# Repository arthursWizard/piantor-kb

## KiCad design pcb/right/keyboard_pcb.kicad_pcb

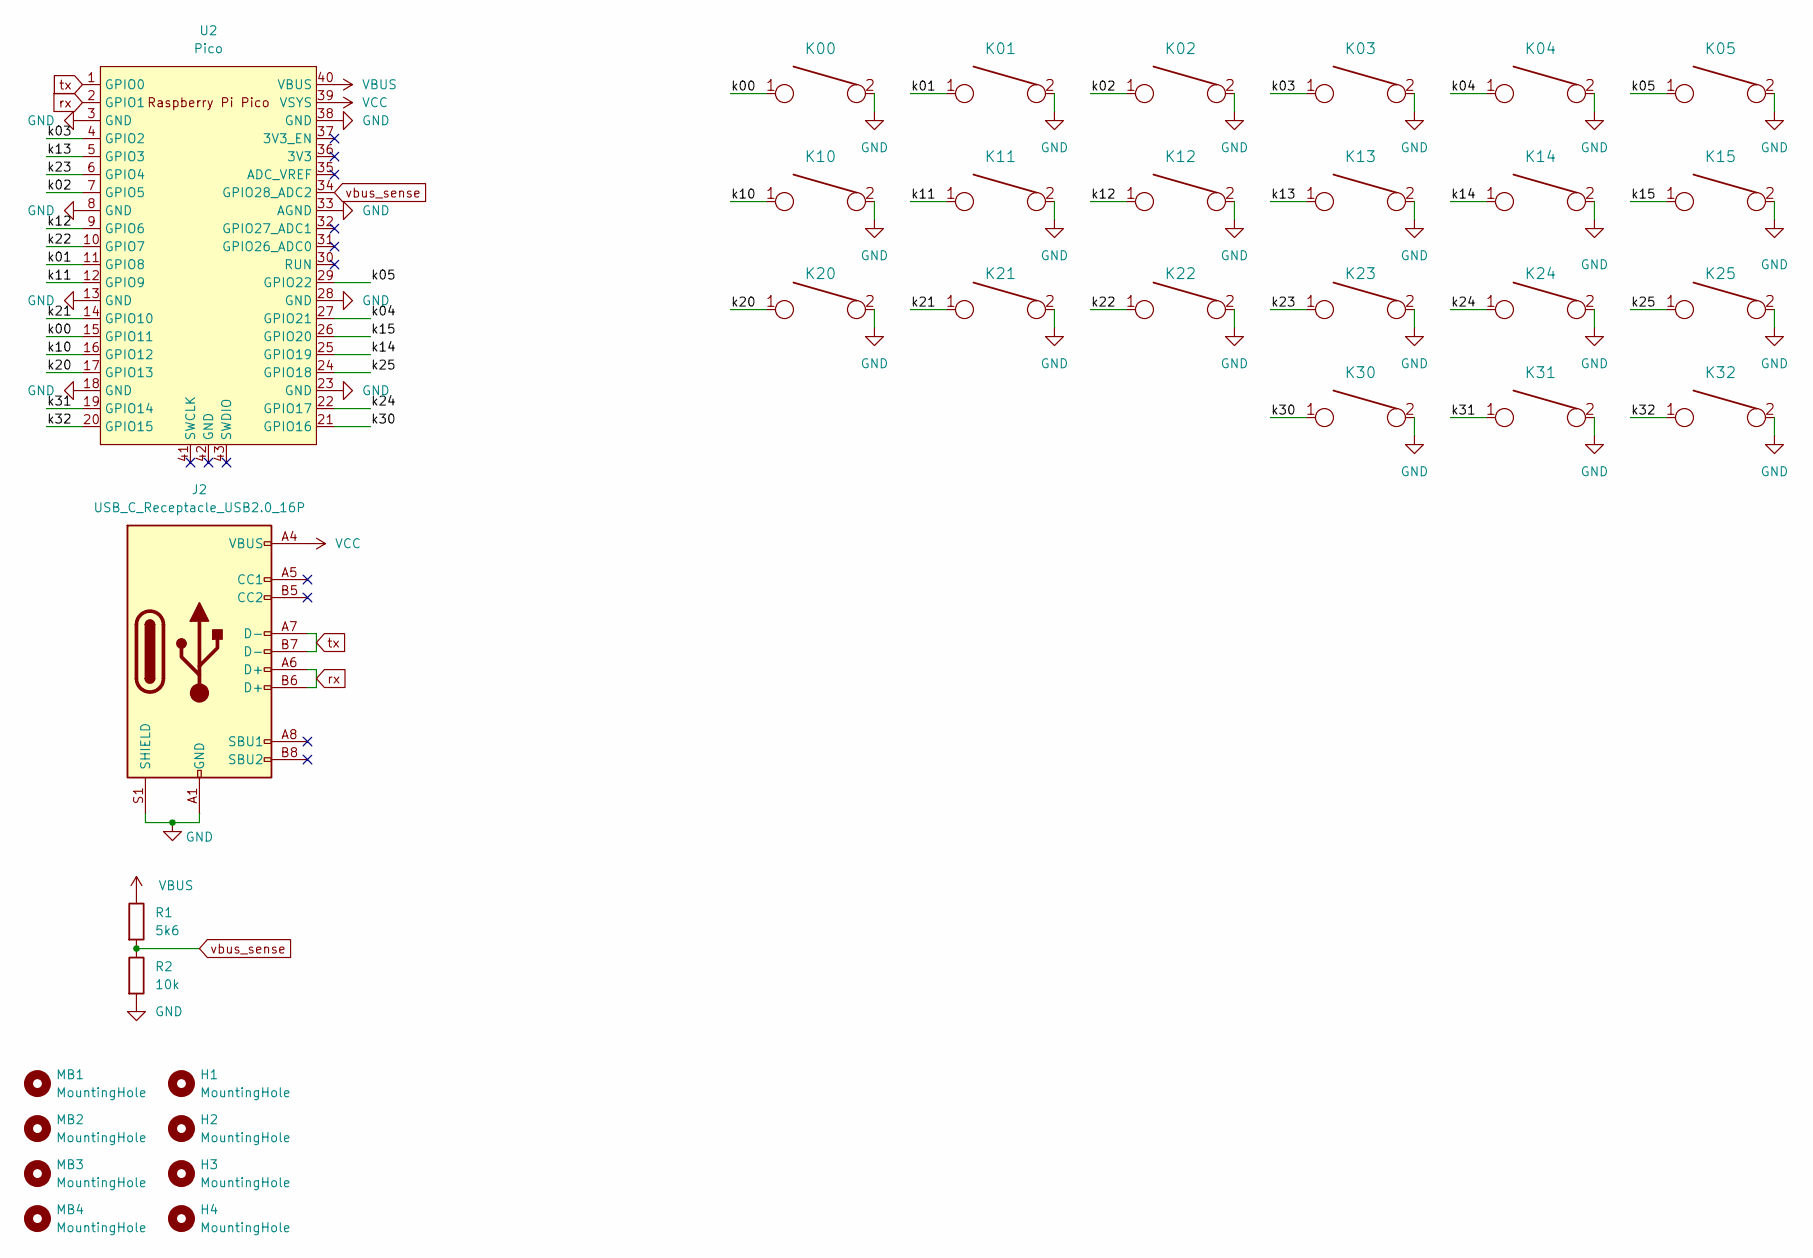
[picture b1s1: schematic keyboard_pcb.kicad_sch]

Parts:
H1, H2, H3, H4: MountingHole; MountingHole_2.2mm_M2-8mm
J2: USB_C_Receptacle_USB2.0_16P; USB_C_Receptacle_Palconn_UTC16-G
K00, K01, K02, K03, K04, K05, K10, K11, K12, K13, K14, K15, K20, K21, K22, K23, K24, K25, K30, K31, K32: KEYSW; SW_PG1350_reversible
MB1, MB2, MB3, MB4: MountingHole; mousebites
R1: 5k6; R_1206_3216Metric_Pad1.30x1.75mm_HandSolder
R2: 10k; R_1206_3216Metric_Pad1.30x1.75mm_HandSolder
U2: Pico; RPi_Pico_SMD_TH

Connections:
/k00: K00.1, U2.15 (GPIO11)
/k01: K01.1, U2.11 (GPIO8)
/k02: K02.1, U2.7 (GPIO5)
/k03: K03.1, U2.4 (GPIO2)
/k04: K04.1, U2.27 (GPIO21)
/k05: K05.1, U2.29 (GPIO22)
/k10: K10.1, U2.16 (GPIO12)
/k11: K11.1, U2.12 (GPIO9)
/k12: K12.1, U2.9 (GPIO6)
/k13: K13.1, U2.5 (GPIO3)
/k14: K14.1, U2.25 (GPIO19)
/k15: K15.1, U2.26 (GPIO20)
/k20: K20.1, U2.17 (GPIO13)
/k21: K21.1, U2.14 (GPIO10)
/k22: K22.1, U2.10 (GPIO7)
/k23: K23.1, U2.6 (GPIO4)
/k24: K24.1, U2.22 (GPIO17)
/k25: K25.1, U2.24 (GPIO18)
/k30: K30.1, U2.21 (GPIO16)
/k31: K31.1, U2.19 (GPIO14)
/k32: K32.1, U2.20 (GPIO15)
GND: J2.A1 (GND), J2.A12 (GND), J2.B1 (GND), J2.B12 (GND), J2.S1 (SHIELD), K00.2, K01.2, K02.2, K03.2, K04.2, K05.2, K10.2, K11.2, K12.2, K13.2, K14.2, K15.2, K20.2, K21.2, K22.2, K23.2, K24.2, K25.2, K30.2, K31.2, K32.2, R2.2, U2.3 (GND), U2.8 (GND), U2.13 (GND), U2.18 (GND), U2.23 (GND), U2.28 (GND), U2.33 (AGND), U2.38 (GND)
VBUS: R1.1, U2.40 (VBUS)
VCC: J2.A4 (VBUS), J2.A9 (VBUS), J2.B4 (VBUS), J2.B9 (VBUS), U2.39 (VSYS)
rx: J2.A6 (D+), J2.B6 (D+), U2.2 (GPIO1)
tx: J2.A7 (D-), J2.B7 (D-), U2.1 (GPIO0)
vbus_sense: R1.2, R2.1, U2.34 (GPIO28_ADC2)

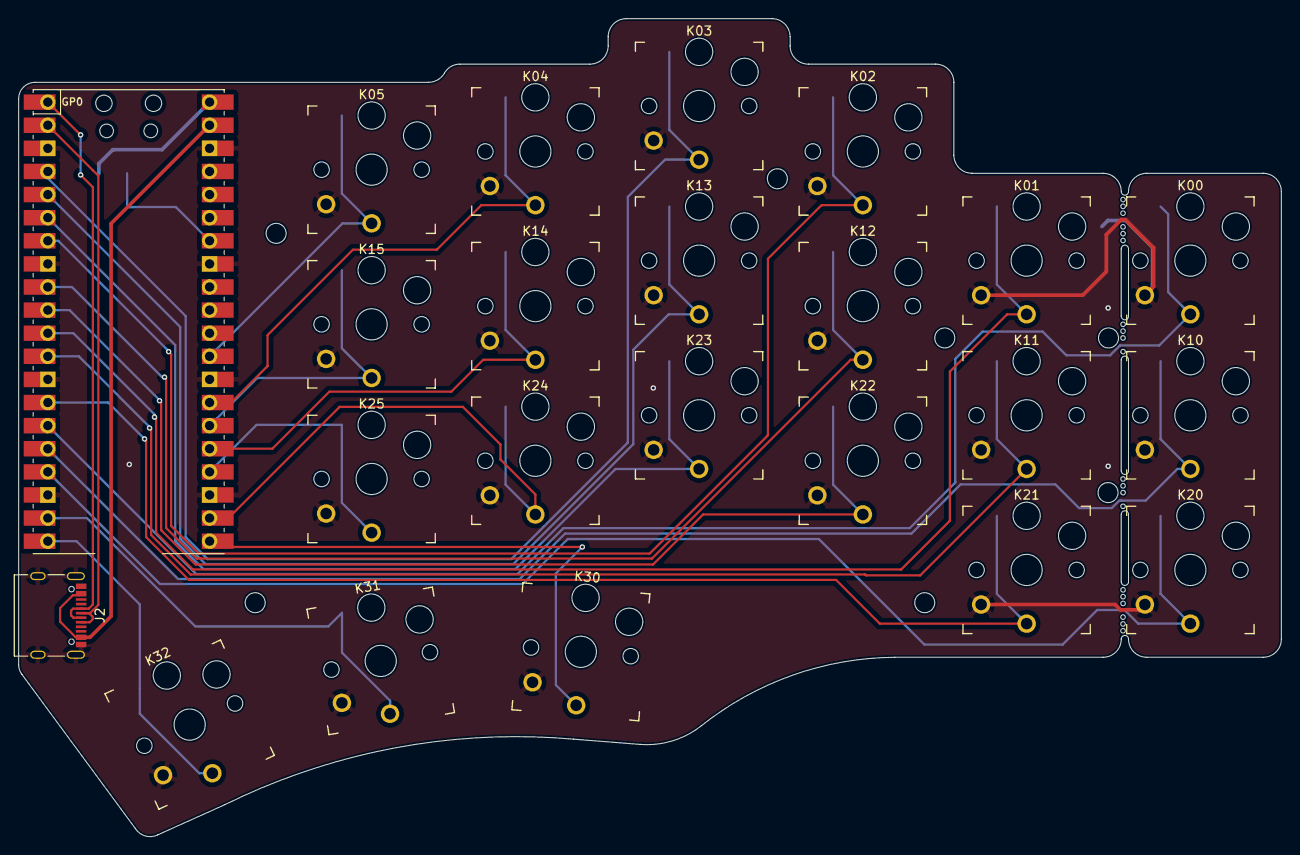
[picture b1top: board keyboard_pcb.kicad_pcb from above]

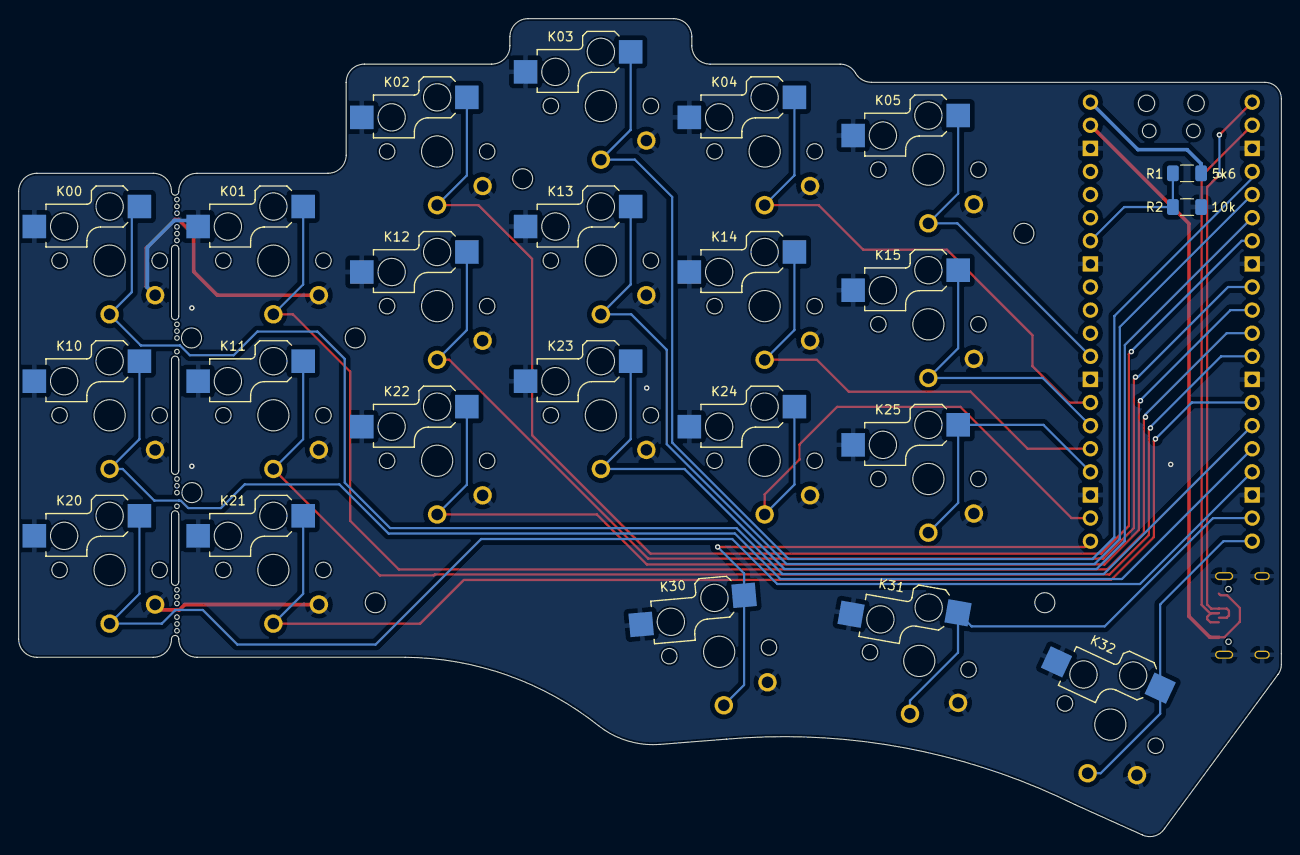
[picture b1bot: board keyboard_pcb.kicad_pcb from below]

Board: 2 copper layers, 138.8 x 89.9 mm, 36 parts (13 on the bottom side), 27 nets.

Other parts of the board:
H1#2, H4#2, H4#3: MountingHole; MountingHole_2.2mm_M2-8mm

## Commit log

2025-05-21 Replace TRRS with USB-C on left side
2025-05-22 Add right side, add fabrication outputs
2025-05-23 Update left zip
2025-06-10 Update right side
